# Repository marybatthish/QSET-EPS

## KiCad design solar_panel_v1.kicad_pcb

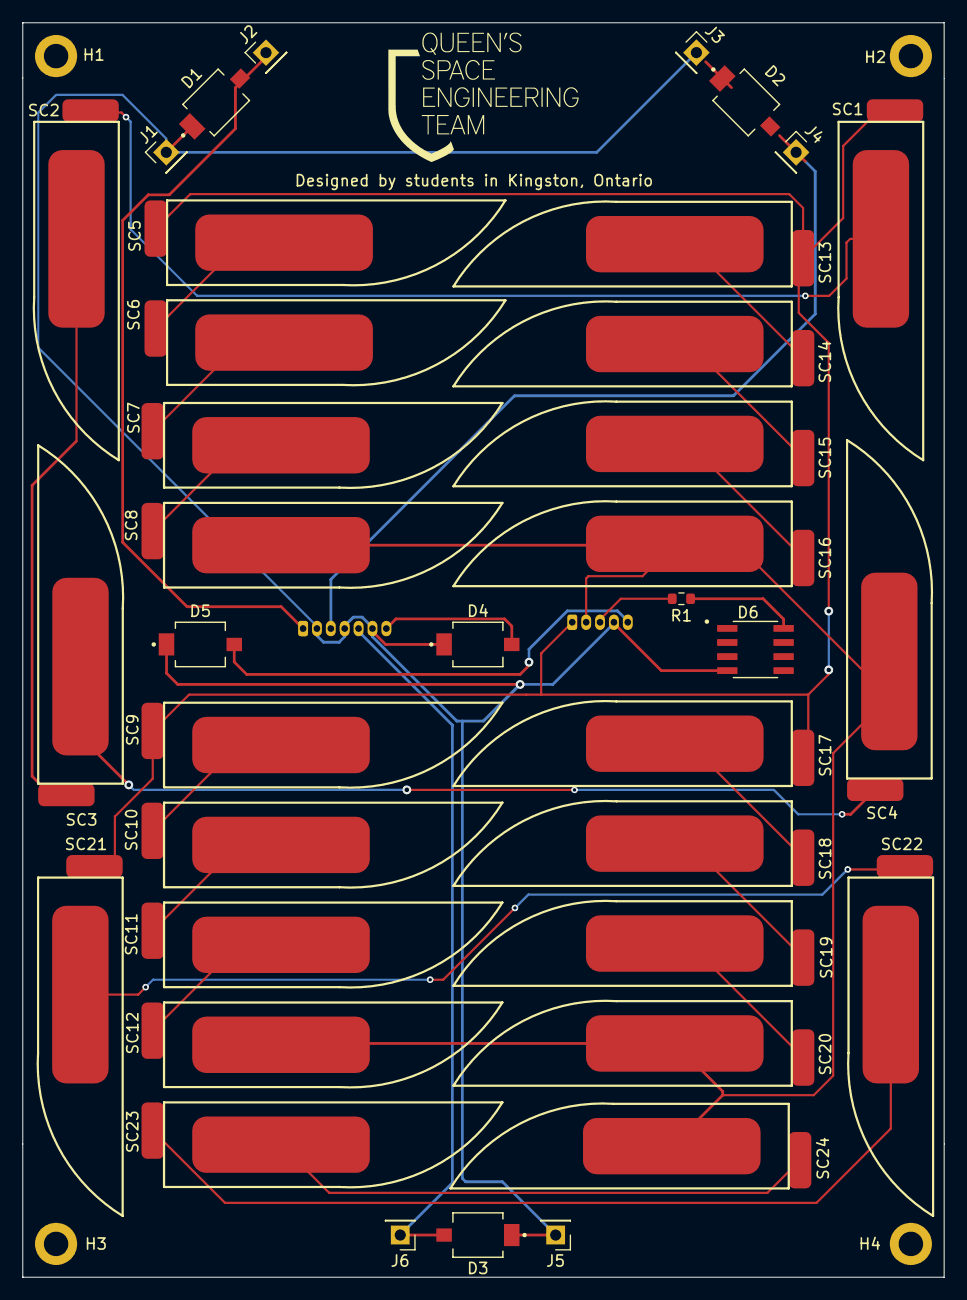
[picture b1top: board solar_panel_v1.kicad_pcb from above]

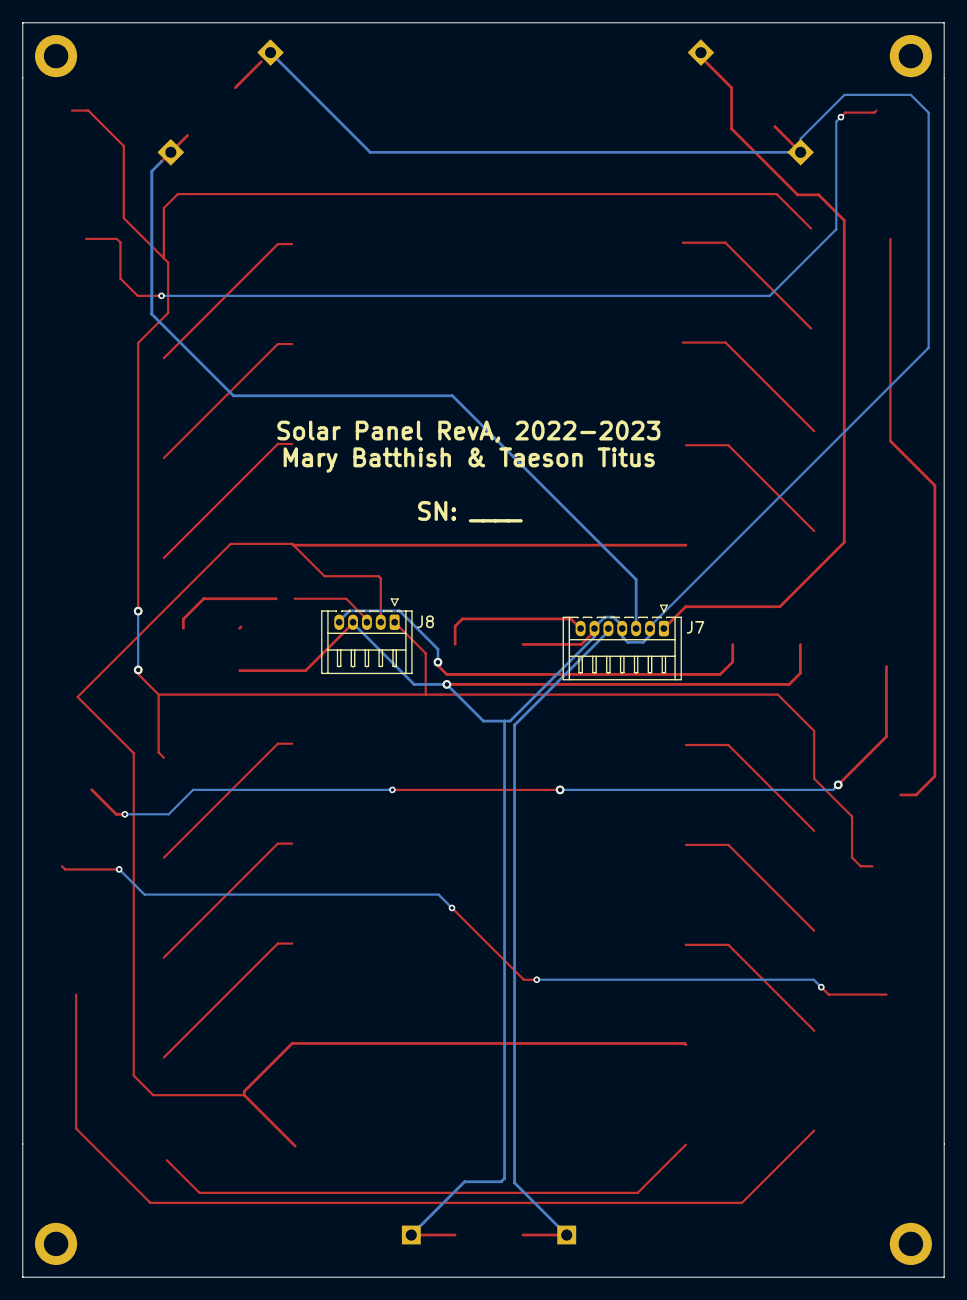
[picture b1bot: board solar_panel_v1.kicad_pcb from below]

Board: 2 copper layers, 83.0 x 113.0 mm, 43 parts (2 on the bottom side), 27 nets.

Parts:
D1, D2, D3, D4, D5: D_Photo; DIO_SFH_2430-Z
D6: D_Temp; SOIC127P600X175-8N
H1, H2, H3, H4: MountingHole; MountingHole_2.2mm_M2_DIN965_Pad
J1, J2, J3, J4, J5, J6: Conn_01x01; PinHeader_1x01_P2.54mm_Vertical
J7: DF13-7P-1.25DS(20); Hirose_DF13-07P-1.25DS_1x07_P1.25mm_Horizontal
J8: DF-13-5P-1.25DS; Hirose_DF13-05P-1.25DS_1x05_P1.25mm_Horizontal
R1: 0; R_0603_1608Metric
SC1, SC2, SC3, SC4, SC5, SC6, SC7, SC8, SC9, SC10, SC11, SC12, SC13, SC14, SC15, SC16, SC17, SC18, SC19, SC20, SC21, SC22, SC23, SC24: Solar_Cell; TrisolX_Solar_Cell

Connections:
ADSC_PD_1: D1.1 (K), J2.1
ADSC_PD_2: D2.1 (K), J4.1
ADSC_PD_3: D3.1 (K), J6.1
ARRAY_PWR: J8.1, SC1.1 (+), SC5.1 (+), SC9.1 (+), SC13.1 (+), SC17.1 (+), SC21.1 (+)
ARRAY_RTN: J8.2, SC4.2 (-), SC8.2 (-), SC12.2 (-), SC16.2 (-), SC20.2 (-), SC24.2 (-)
EPS_PD_1: D5.1 (K), J8.5
EPS_TMP_1: J8.3, R1.2
GND: D1.2 (A), D2.2 (A), D3.2 (A), D4.2 (A), D5.2 (A), D6.4, J1.1, J3.2, J5.1, J7.2, J7.4, J7.6, J8.4
unnamed: D6.8, R1.1
unnamed: SC1.2 (-), SC2.1 (+)
unnamed: SC2.2 (-), SC3.1 (+)
unnamed: SC3.2 (-), SC4.1 (+)
unnamed: SC5.2 (-), SC6.1 (+)
unnamed: SC6.2 (-), SC7.1 (+)
unnamed: SC7.2 (-), SC8.1 (+)
unnamed: SC9.2 (-), SC10.1 (+)
unnamed: SC10.2 (-), SC11.1 (+)
unnamed: SC11.2 (-), SC12.1 (+)
unnamed: SC13.2 (-), SC14.1 (+)
unnamed: SC14.2 (-), SC15.1 (+)
unnamed: SC15.2 (-), SC16.1 (+)
unnamed: SC17.2 (-), SC18.1 (+)
unnamed: SC18.2 (-), SC19.1 (+)
unnamed: SC19.2 (-), SC20.1 (+)
unnamed: SC21.2 (-), SC22.1 (+)
unnamed: SC22.2 (-), SC23.1 (+)
unnamed: SC23.2 (-), SC24.1 (+)
